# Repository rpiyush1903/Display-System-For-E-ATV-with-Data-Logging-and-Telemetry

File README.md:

# Display and Safety System for an E-ATV Using CAN Bus Communication Protocol

## Description

This project is a custom dashboard and safety unit that I built for our electric All-Terrain Vehicle. It sits between the driver and the battery pack, doing two jobs at once: showing the driver what the battery is doing in real time, and acting as a safety switch that can cut power to the tractive system if something goes wrong.

The unit reads data directly from our JBD Battery Management System over CAN bus and shows it on a TFT display mounted on the dash Pack voltage, current draw (or charge current), state of charge (SoC), and pack temperature. It also drives a relay that can de-energize the main contactors, either automatically when a fault is detected or manually during testing.

Everything runs on an ATMega328P microcontroller, with an MCP2515 module handling the CAN interface, and the whole thing is built onto a custom PCB so it can survive the vibration and environment of off-road racing.

## Why I Built This

When you're racing an e-ATV, the battery pack is both the thing that makes the vehicle go and the thing most likely to cause a serious problem if it's mismanaged. 

**Charging and pack safety.** A lithium pack that's overcharged, over-discharged, or running too hot can fail badly, and on a race vehicle there isn't always someone watching a laptop connected to the BMS. I wanted a hardware safety interlock that sits close to the pack and can isolate it the moment something crosses a safe limit, rather than relying on the driver to notice a problem and react in time. 

Also there should be an hardware safety interlock to prevent simultaneous charging and operation of vehicle ( battery should not get charged when vehicle is ready to drive)

**Driver awareness.** Beyond safety, the driver genuinely needs to know what the battery is doing while driving — voltage, current draw, temperature, and remaining charge. Without this, the driver is flying blind: they don't know if they're pushing the pack too hard, how much charge is left for the rest of a heat, or whether the pack is running hotter than it should. A simple, readable display on the dash solves that, and having it double as a diagnostic tool during pit stops and testing was a natural extension.

Putting both of these on one board also meant fewer separate systems, less wiring, and reduced clutter in the vehicle.

## How I Did It

I started from the JBD BMS's CAN output, since that's already generating the data I needed I didn't want to add extra sensors when the BMS was already measuring everything.

**Reading the BMS over CAN.** I used an MCP2515 CAN controller (SPI interface) to talk to the BMS at 500kbps. The BMS broadcasts on a few standard IDs, and I parsed the ones that matter for the dashboard:

| CAN ID | Data |
| :--- | :--- |
| `0x100` | Pack voltage and current |
| `0x101` | State of charge 
| `0x105` | Pack temperature 

Since the BMS doesn't just keep streaming data forever on its own, I have the microcontroller send a small keep-alive frame (`0x5A`) periodically to the BMS's target IDs, which keeps the connection alive and the data flowing.

**Showing it to the driver.** The parsed values get pushed to a TFT display using the `TFT_eSPI` library, connected over the hardware SPI bus. I set up `User_Setup.h` to match the exact driver and pinout of the display I used, since getting this wrong is the most common reason the display doesn't come up at all.

**The safety side.** A relay is wired to a dedicated GPIO pin (pin 5 in the diagnostic build). HIGH keeps the relay de-energized and power flowing normally; pulling it LOW cuts power by opening the main contactors. This lets the firmware isolate the pack automatically if a reading goes outside safe limits, and it also gives me a manual way to cut power during bench testing without touching the high-voltage wiring directly.

**Putting it on one board.** Once the logic was working on a breadboard, I moved everything onto a custom PCB. The main reason was reliability . An ATV shakes a lot, and loose header connections are a common failure point. I also made sure to physically separate the high-speed SPI lines (display and CAN) from the relay switching lines on the layout, since the relay can introduce electrical noise that was causing flicker on the display and occasional glitches on the CAN bus during earlier tests.

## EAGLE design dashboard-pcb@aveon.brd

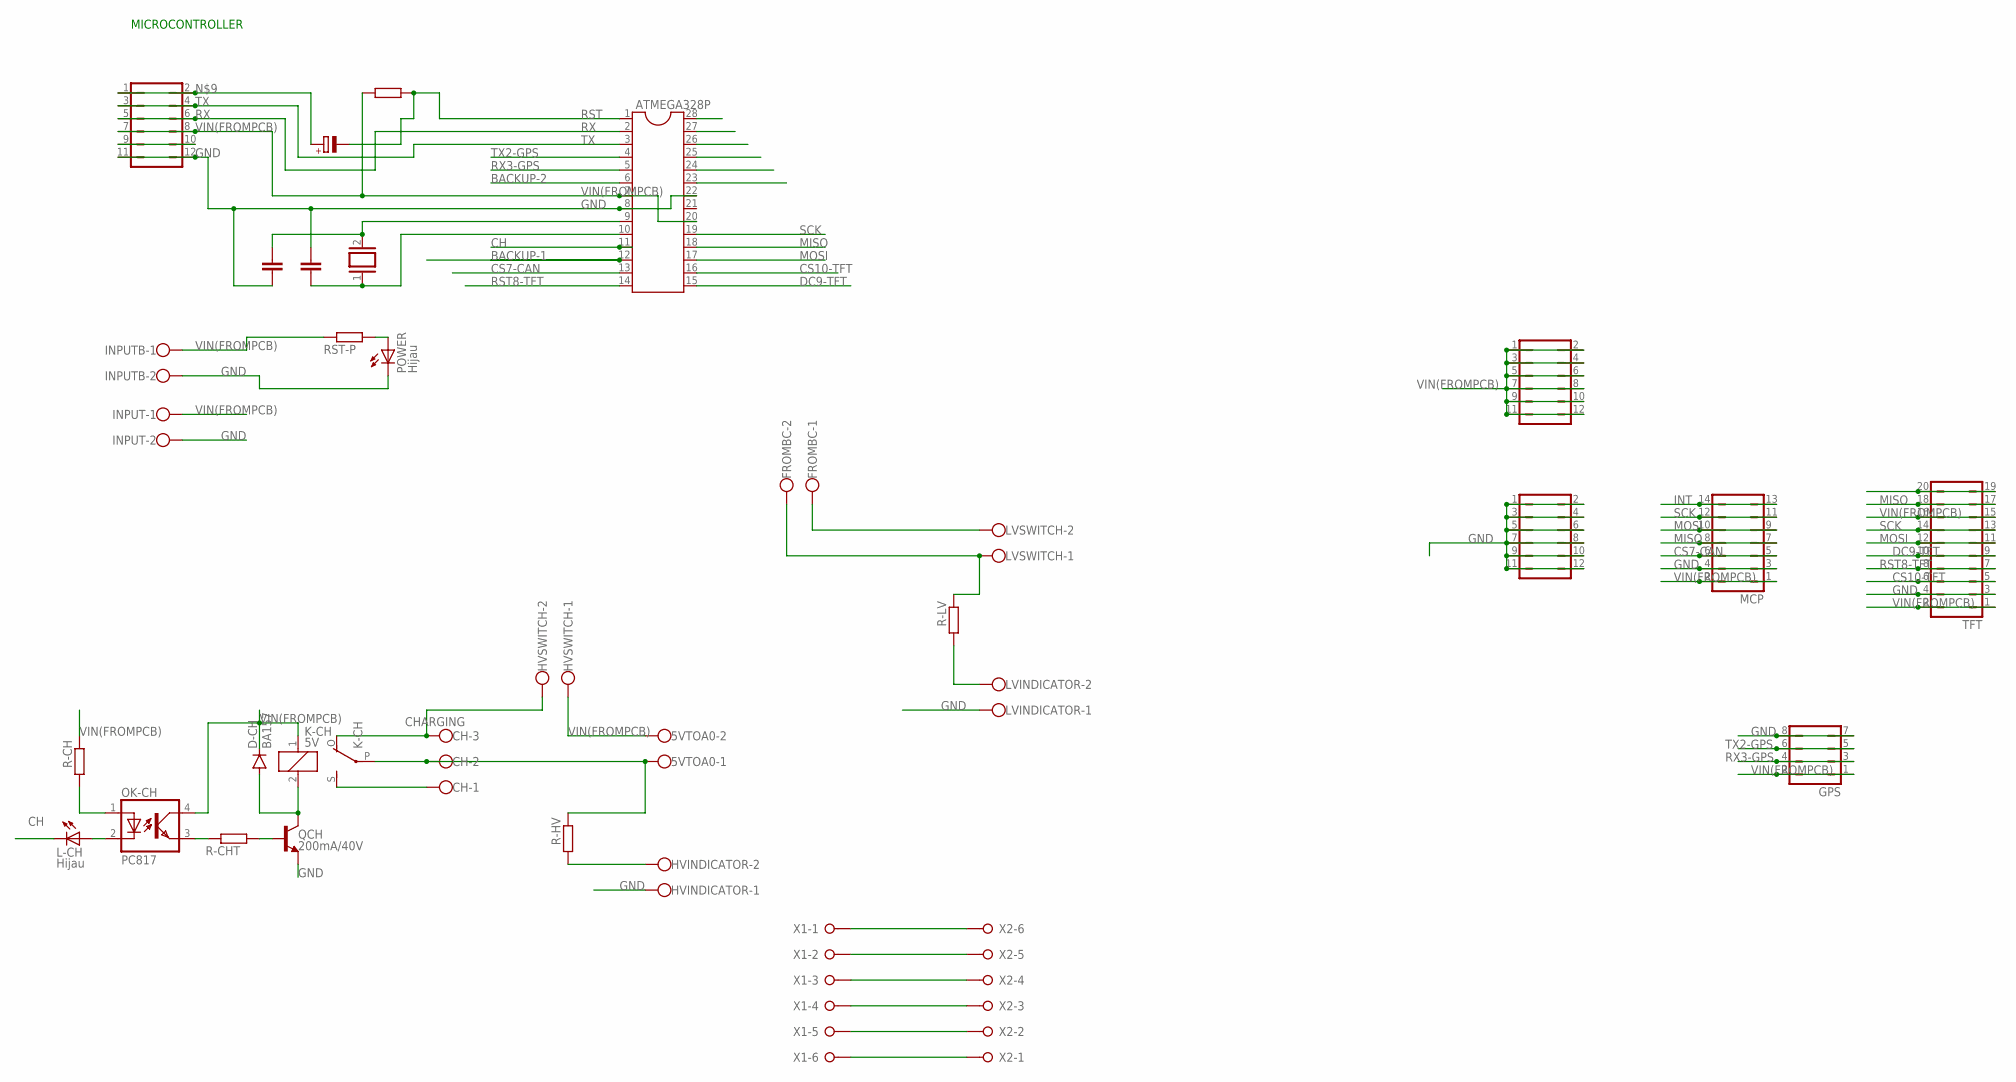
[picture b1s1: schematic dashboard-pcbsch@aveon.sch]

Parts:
5VTOA0: W237-102
ATMEGA328P: DIL28-3
C1, C2: C-EU025-030X050; C025-030X050
CH: CHARGING; W237-103
CRYSTAL: XTAL/S; QS
D-CH: BA157; P1-10
FROMBC: W237-102
GPS: JP4Q
GROUND: JP6Q
HVINDICATOR: W237-102
HVSWITCH: W237-102
INPUT: W237-102
INPUTB: W237-102
K-CH: 5V; ZF112
L-CH: Hijau; LED3MM
LVINDICATOR: W237-102
LVSWITCH: W237-102
MCP: JP7Q
OK-CH: PC817; DIL04
POWER: Hijau; LED3MM
PROGRAMMER: JP6Q
QCH: 200mA/40V; TO-92
R-CH: R-EU_0204/7; 0204/7
R-CHT: R-EU_0204/7; 0204/7
R-HV: R-EU_0204/7; 0204/7
R-LV: R-EU_0204/7; 0204/7
RST-C: CPOL-EUE2.5-6; E2,5-6
RST-P: R-EU_0204/7; 0204/7
RST-R: R-EU_0204/7; 0204/7
TFT: JP10Q
VIN(FROMPC): JP6Q
X1, X2: W237-06P; W237-6P

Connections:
BACKUP-1: ATMEGA328P.12
BACKUP-2: ATMEGA328P.6
CH: ATMEGA328P.11, L-CH.K (C)
CS7-CAN: ATMEGA328P.13, MCP.5, MCP.6
CS10-TFT: ATMEGA328P.16, TFT.5, TFT.6
DC9-TFT: ATMEGA328P.15, TFT.9, TFT.10
GND: ATMEGA328P.8, ATMEGA328P.22, C1.1, C2.2, GPS.7, GPS.8, GROUND.1, GROUND.2, GROUND.3, GROUND.4, GROUND.5, GROUND.6, GROUND.7, GROUND.8, GROUND.9, GROUND.10, GROUND.11, GROUND.12, HVINDICATOR.1, INPUT.2, INPUTB.2, LVINDICATOR.1, MCP.3, MCP.4, POWER.K (C), PROGRAMMER.11, PROGRAMMER.12, QCH.1 (E), TFT.3, TFT.4
INT: MCP.13, MCP.14
MISO: ATMEGA328P.18, MCP.7, MCP.8, TFT.17, TFT.18
MOSI: ATMEGA328P.17, MCP.9, MCP.10, TFT.11, TFT.12
unnamed: POWER.A, RST-P.1
unnamed: FROMBC.1, LVSWITCH.2
unnamed: FROMBC.2, LVSWITCH.1, R-LV.2
unnamed: LVINDICATOR.2, R-LV.1
unnamed: PROGRAMMER.1, PROGRAMMER.2, RST-C.+
unnamed: ATMEGA328P.9, C1.2, CRYSTAL.2
unnamed: X1.1, X2.6
unnamed: X1.2, X2.5
unnamed: X1.3, X2.4
unnamed: X1.4, X2.3
unnamed: L-CH.A, OK-CH.2 (C)
unnamed: CH.3, HVSWITCH.2, K-CH.O
unnamed: OK-CH.1 (A), R-CH.1
unnamed: OK-CH.3 (EMIT), R-CHT.2
unnamed: D-CH.A, K-CH.2, QCH.3 (C)
unnamed: QCH.2 (B), R-CHT.1
unnamed: CH.1, K-CH.S
unnamed: 5VTOA0.1, CH.2, K-CH.P, R-HV.2
unnamed: X1.5, X2.2
unnamed: HVINDICATOR.2, R-HV.1
unnamed: X1.6, X2.1
unnamed: TFT.19, TFT.20
unnamed: ATMEGA328P.10, C2.1, CRYSTAL.1
unnamed: PROGRAMMER.9, PROGRAMMER.10
RST: ATMEGA328P.1, RST-C.-, RST-R.2
RST8-TFT: ATMEGA328P.14, TFT.7, TFT.8
RX: ATMEGA328P.2, PROGRAMMER.5, PROGRAMMER.6
RX3-GPS: ATMEGA328P.5, GPS.3, GPS.4
SCK: ATMEGA328P.19, MCP.11, MCP.12, TFT.13, TFT.14
TX: ATMEGA328P.3, PROGRAMMER.3, PROGRAMMER.4
TX2-GPS: ATMEGA328P.4, GPS.5, GPS.6
VIN(FROMPCB): 5VTOA0.2, ATMEGA328P.7, ATMEGA328P.20, D-CH.C, GPS.1, GPS.2, HVSWITCH.1, INPUT.1, INPUTB.1, K-CH.1, MCP.1, MCP.2, OK-CH.4 (COL), PROGRAMMER.7, PROGRAMMER.8, R-CH.2, RST-P.2, RST-R.1, TFT.1, TFT.2, TFT.15, TFT.16, VIN(FROMPC).1, VIN(FROMPC).2, VIN(FROMPC).3, VIN(FROMPC).4, VIN(FROMPC).5, VIN(FROMPC).6, VIN(FROMPC).7, VIN(FROMPC).8, VIN(FROMPC).9, VIN(FROMPC).10, VIN(FROMPC).11, VIN(FROMPC).12

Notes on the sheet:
MICROCONTROLLER

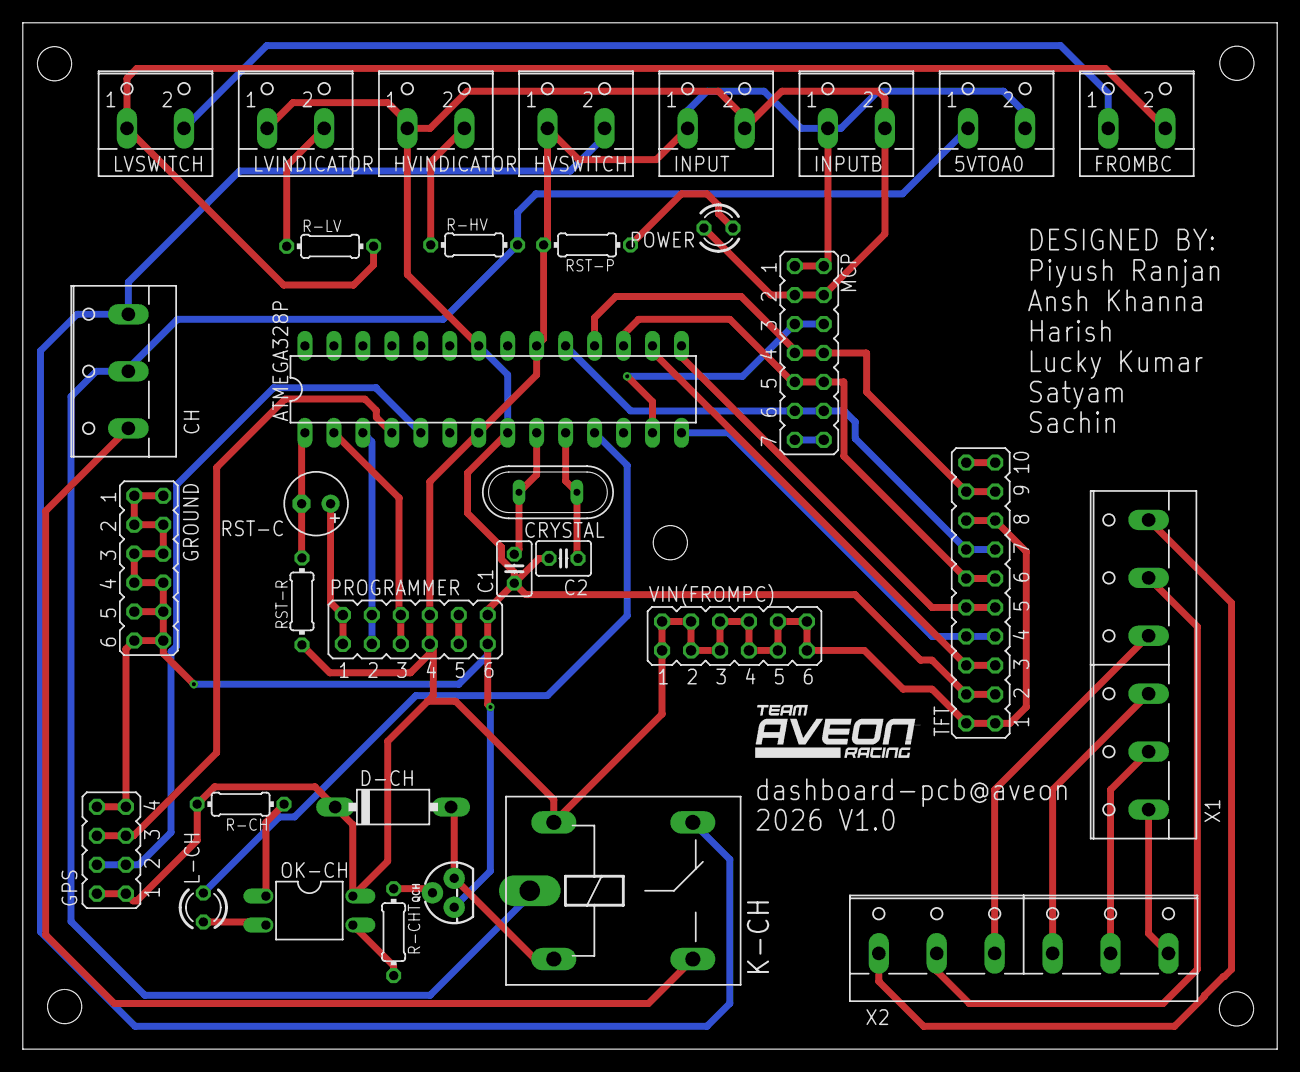
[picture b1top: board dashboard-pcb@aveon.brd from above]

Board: 2 copper layers, 110.0 x 90.0 mm, 34 parts (0 on the bottom side), 40 nets.

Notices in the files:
parts and their libraries:
SparkFun-DiscreteSemi: Licensing: Creative Commons ShareAlike 4.0 International - https://creativecommons.org/licenses/by-sa/4.0
